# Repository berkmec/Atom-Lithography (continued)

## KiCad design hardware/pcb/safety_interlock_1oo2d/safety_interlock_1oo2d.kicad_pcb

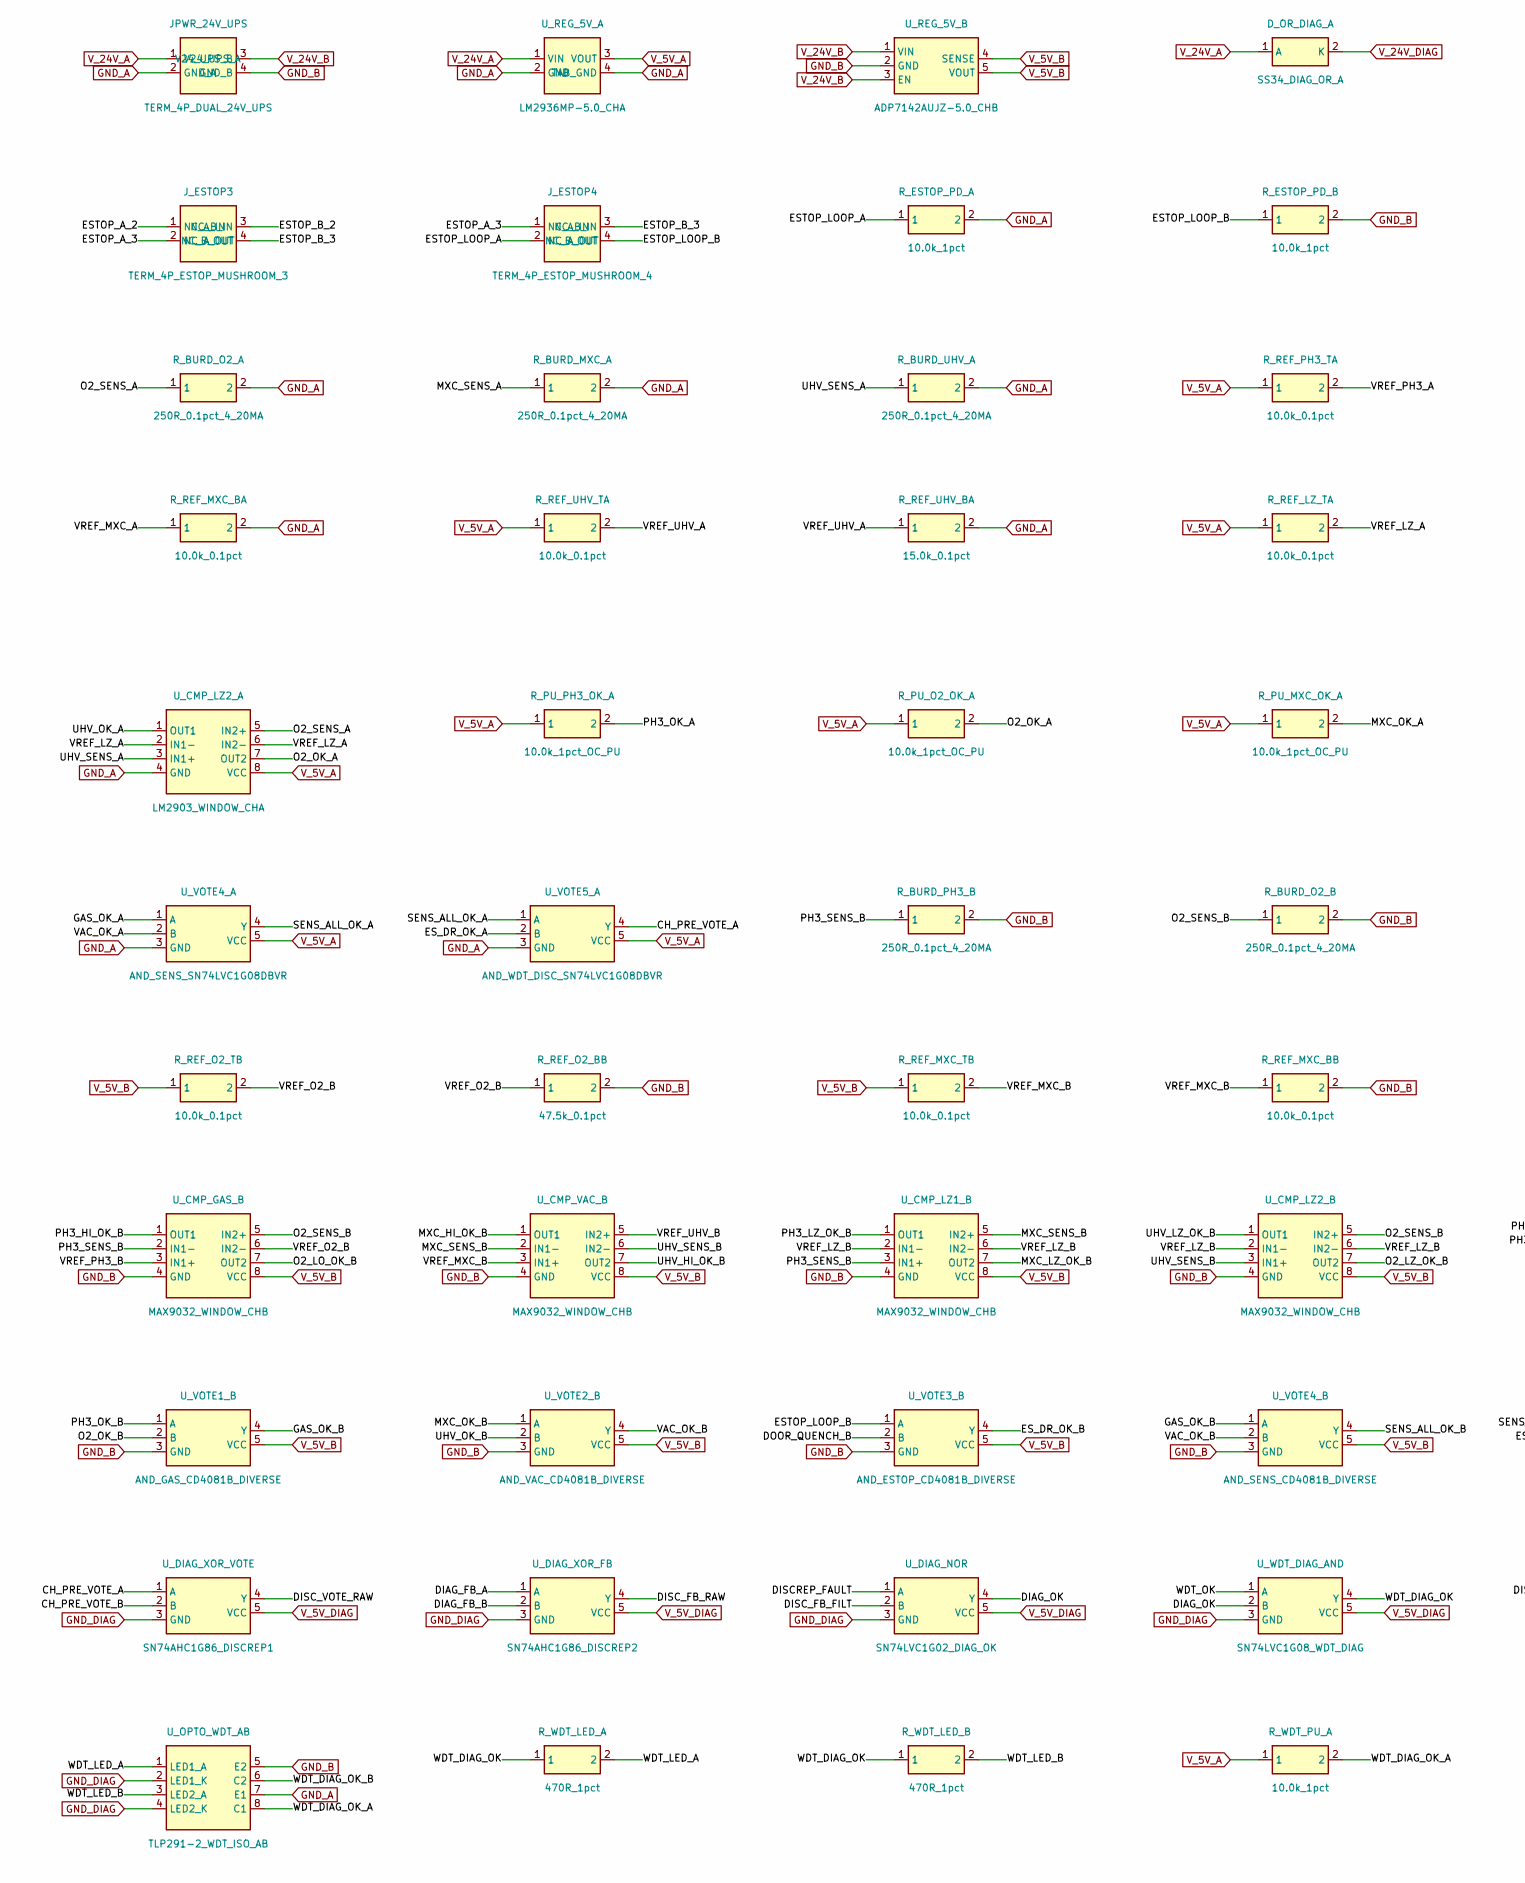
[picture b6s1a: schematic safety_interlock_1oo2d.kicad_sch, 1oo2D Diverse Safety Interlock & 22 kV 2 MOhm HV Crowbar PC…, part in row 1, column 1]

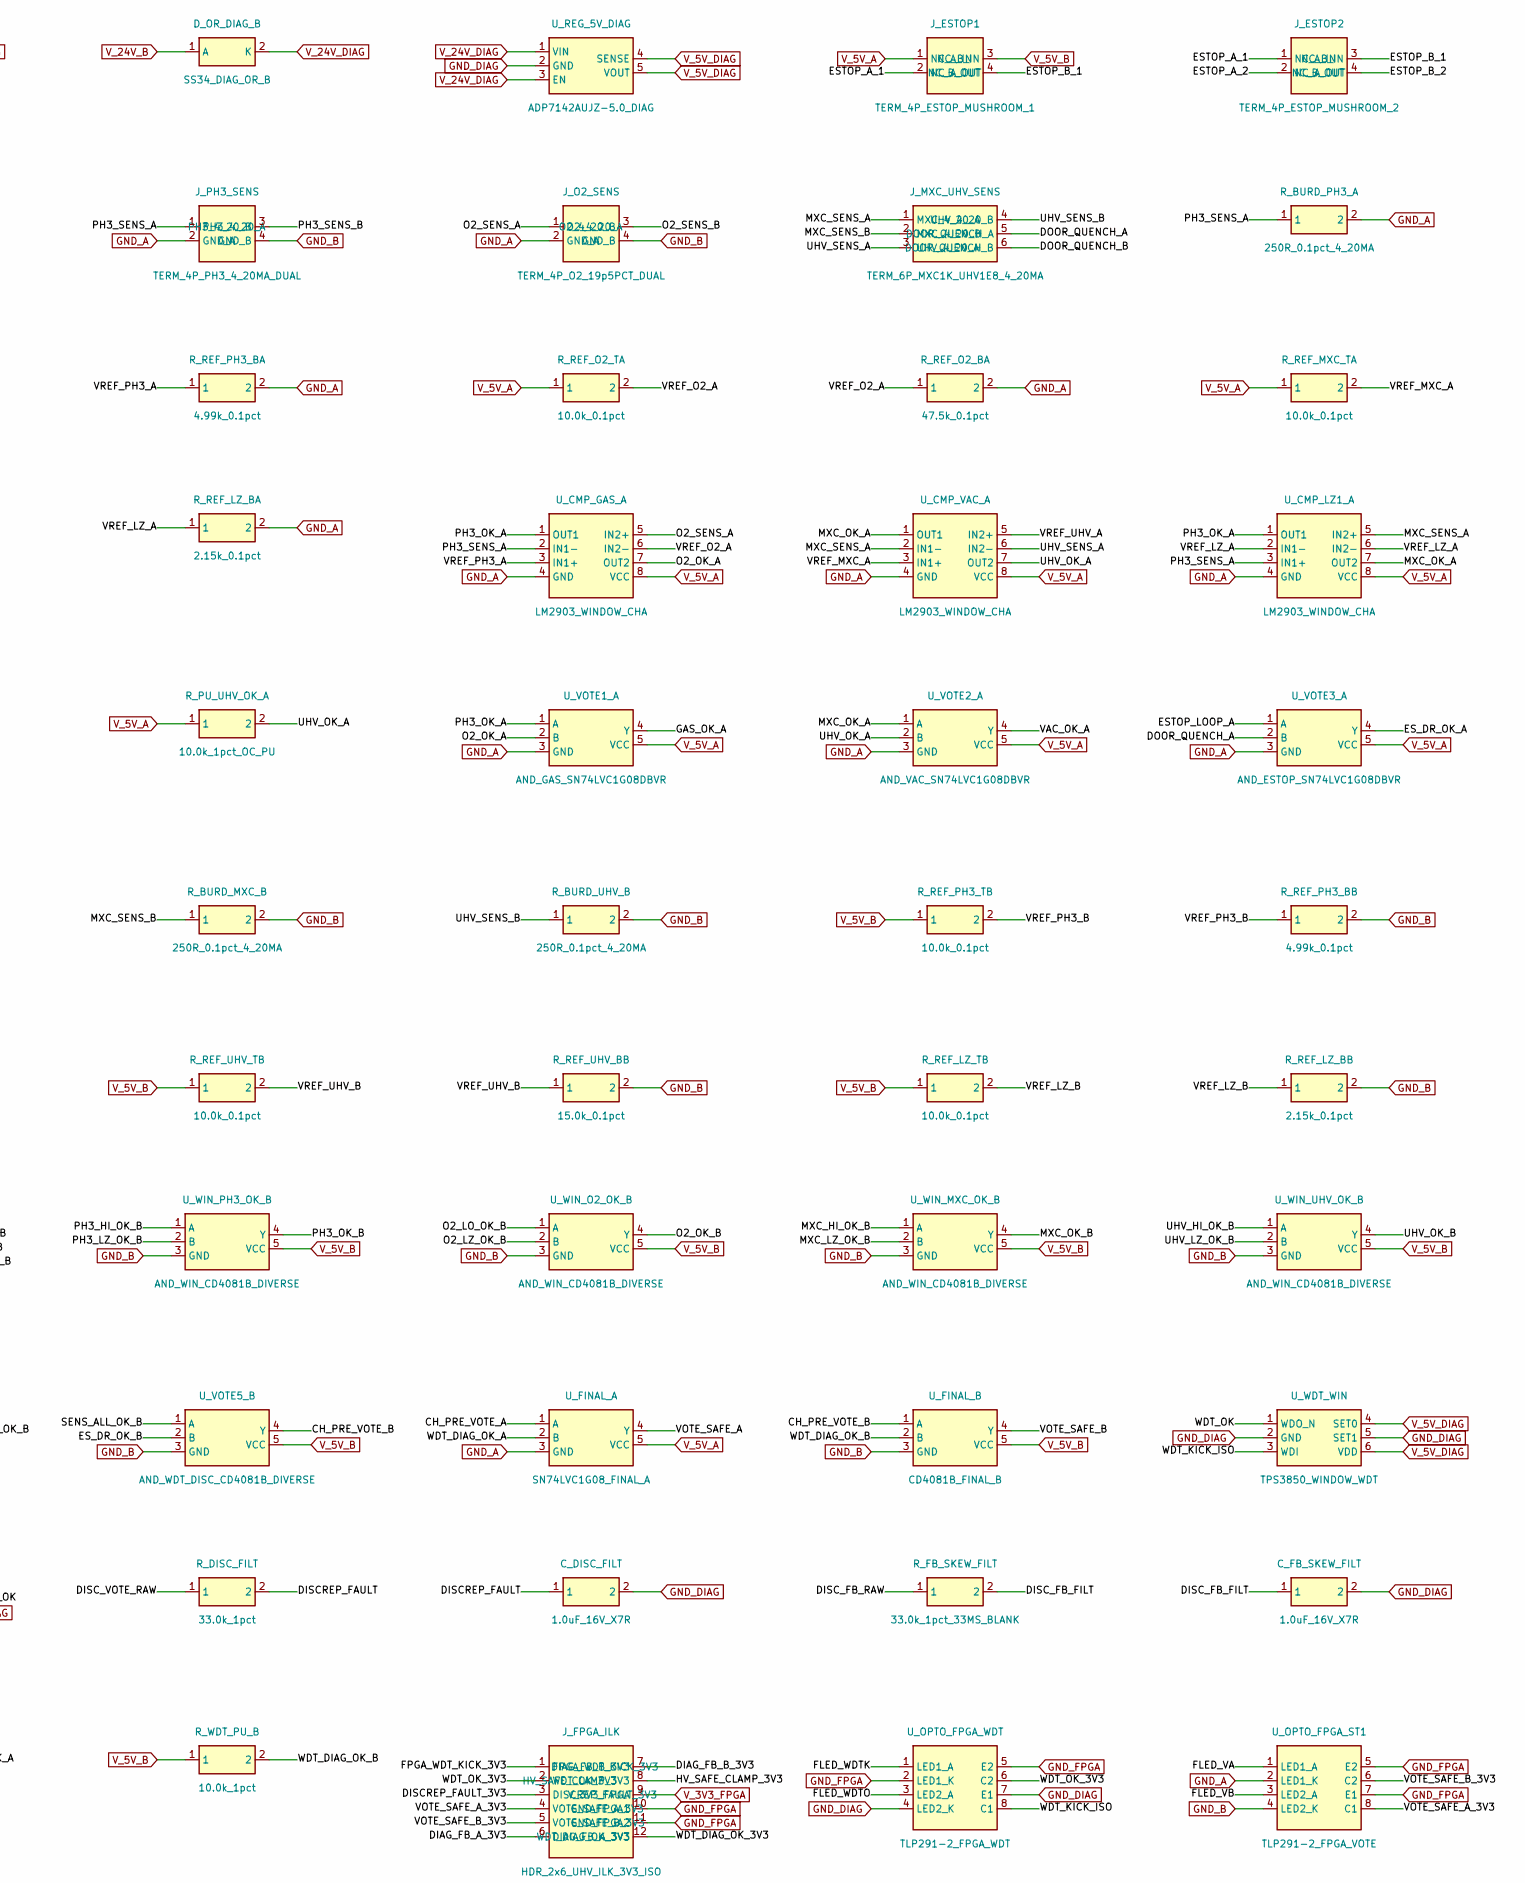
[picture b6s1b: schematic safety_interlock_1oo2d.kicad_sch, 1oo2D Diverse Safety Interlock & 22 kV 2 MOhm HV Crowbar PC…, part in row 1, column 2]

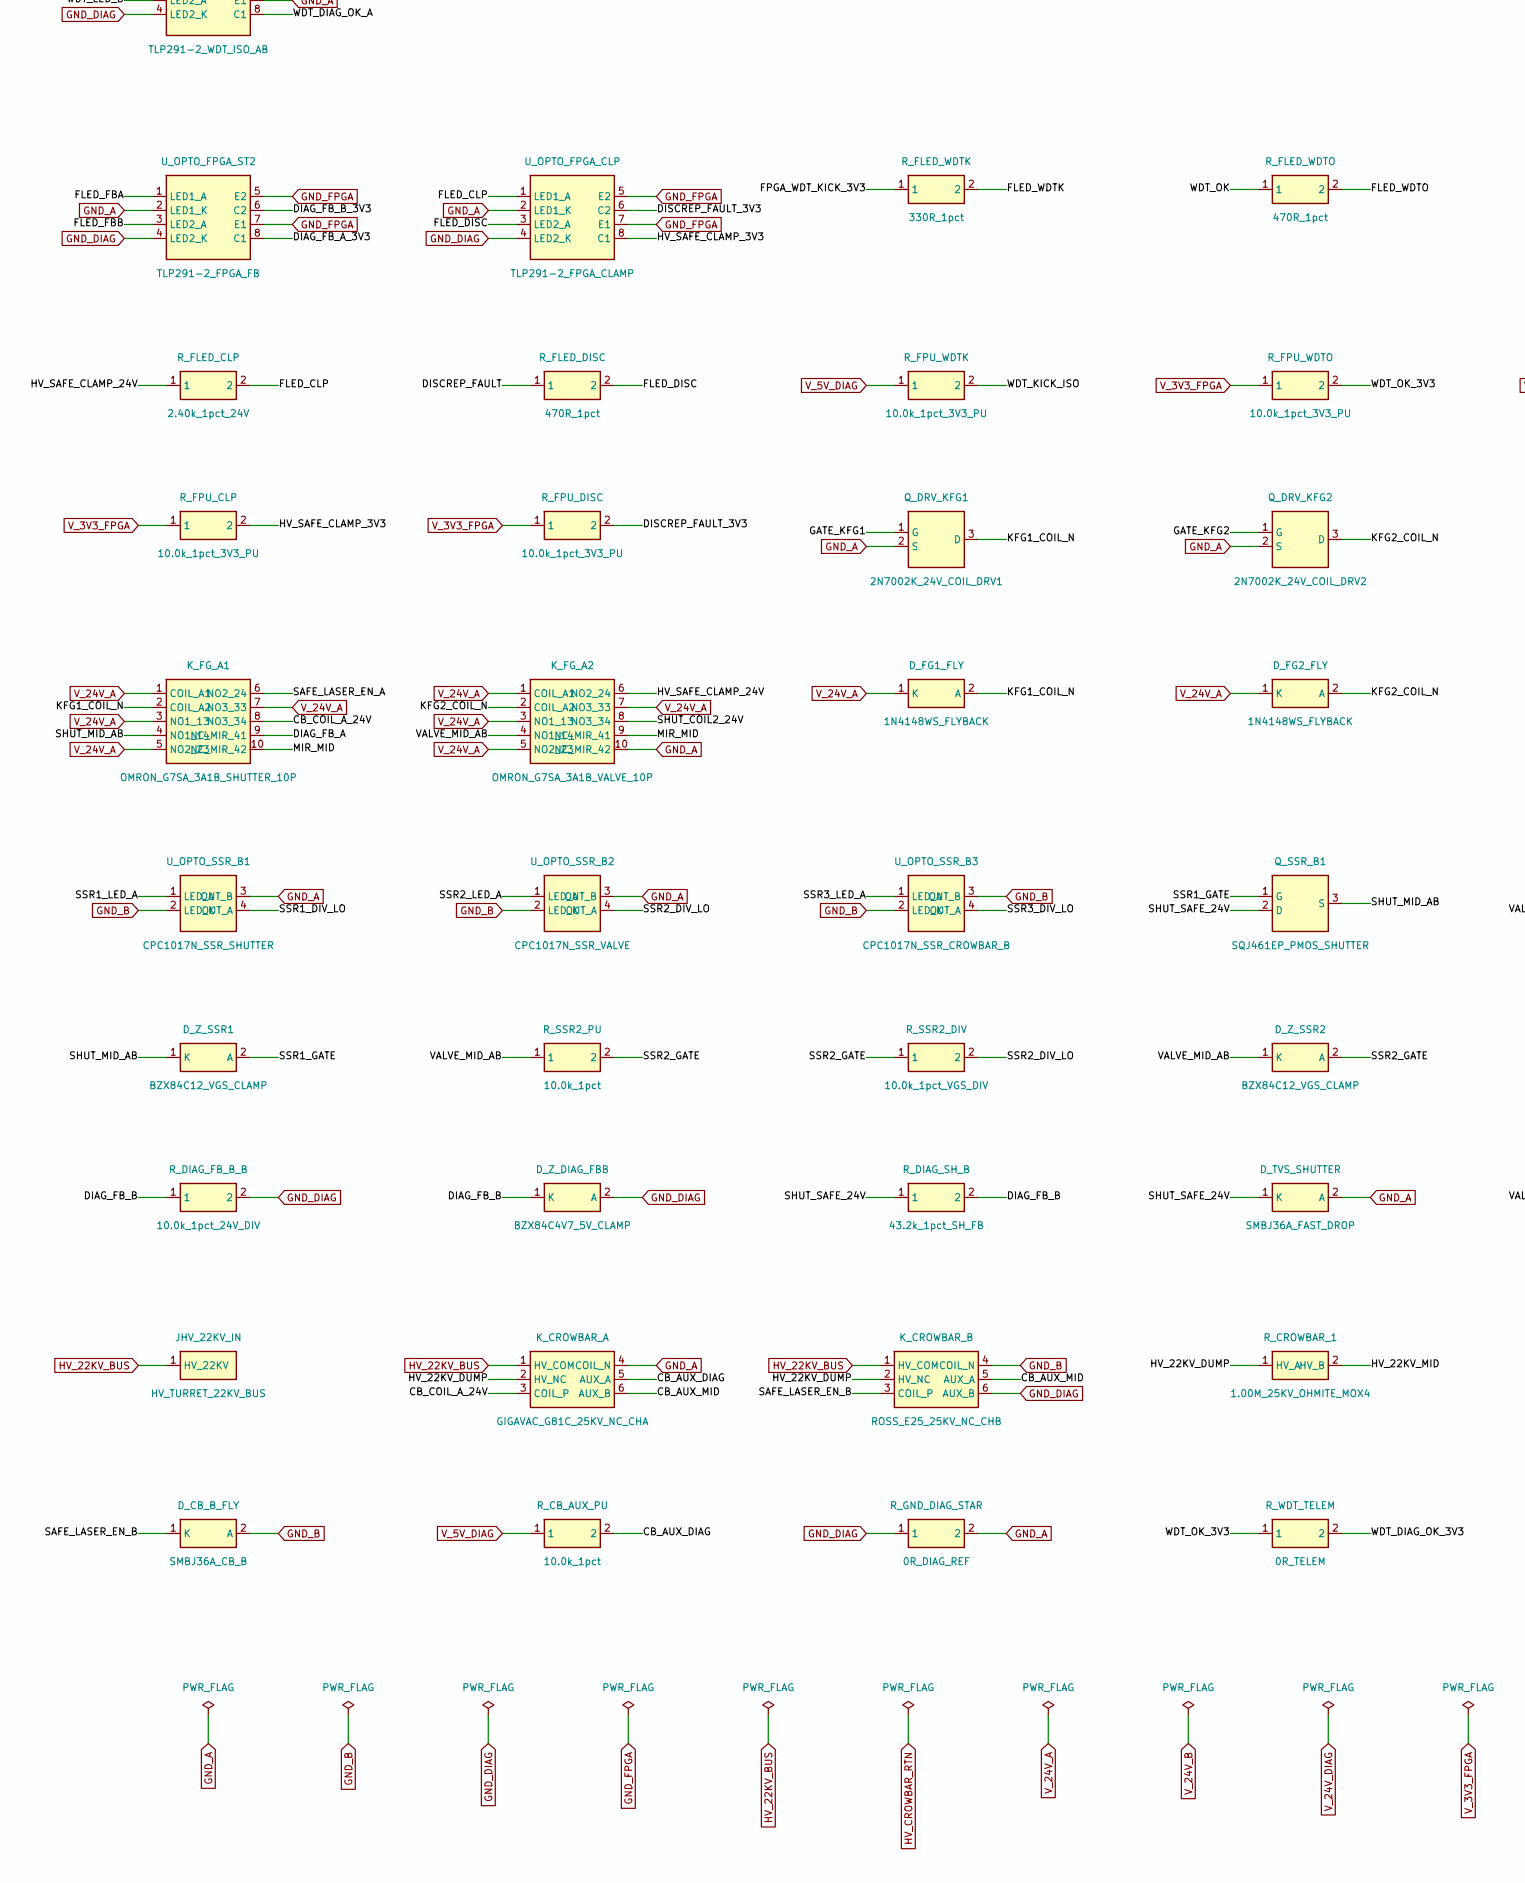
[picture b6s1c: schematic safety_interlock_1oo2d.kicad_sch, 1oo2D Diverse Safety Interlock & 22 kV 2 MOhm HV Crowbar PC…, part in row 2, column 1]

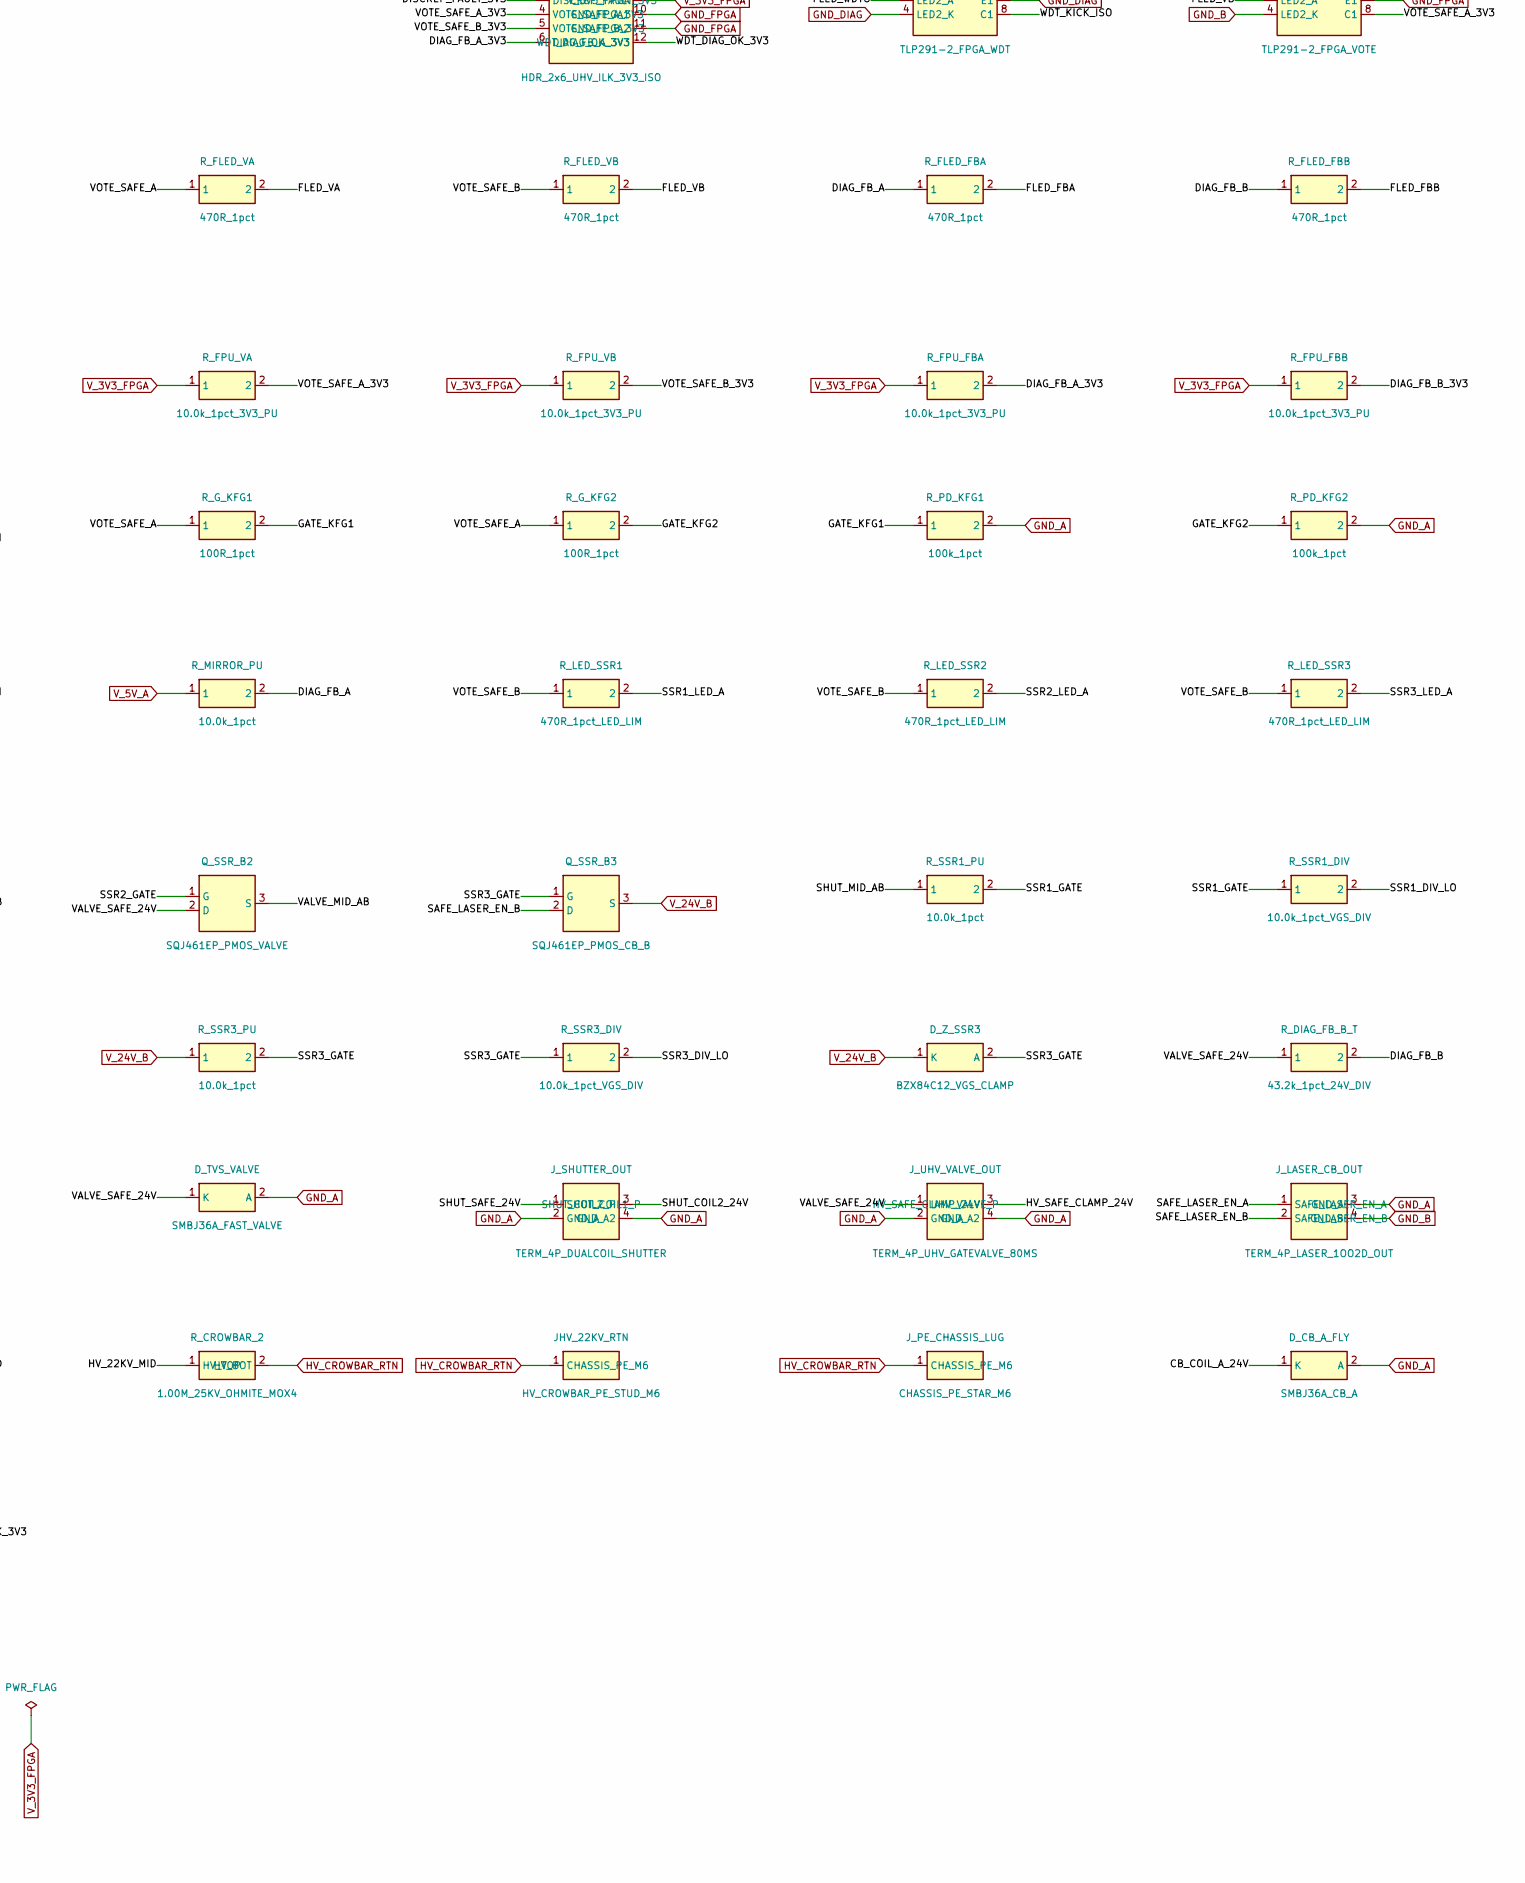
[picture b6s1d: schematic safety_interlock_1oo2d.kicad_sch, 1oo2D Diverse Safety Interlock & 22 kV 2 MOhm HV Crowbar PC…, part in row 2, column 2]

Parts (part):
C_DISC_FILT: 1.0uF_16V_X7R; C_0603_1608Metric; MPN 1.0uF_16V_X7R
C_FB_SKEW_FILT: 1.0uF_16V_X7R; C_0603_1608Metric; MPN 1.0uF_16V_X7R
D_CB_A_FLY: SMBJ36A_CB_A; D_1206_3216Metric; MPN SMBJ36A_CB_A
D_CB_B_FLY: SMBJ36A_CB_B; D_1206_3216Metric; MPN SMBJ36A_CB_B
D_FG1_FLY, D_FG2_FLY: 1N4148WS_FLYBACK; D_0805_2012Metric; MPN 1N4148WS_FLYBACK
D_OR_DIAG_A: SS34_DIAG_OR_A; D_0805_2012Metric; MPN SS34_DIAG_OR_A
D_OR_DIAG_B: SS34_DIAG_OR_B; D_0805_2012Metric; MPN SS34_DIAG_OR_B
D_TVS_SHUTTER: SMBJ36A_FAST_DROP; D_1206_3216Metric; MPN SMBJ36A_FAST_DROP
D_TVS_VALVE: SMBJ36A_FAST_VALVE; D_1206_3216Metric; MPN SMBJ36A_FAST_VALVE
D_Z_DIAG_FBB: BZX84C4V7_5V_CLAMP; D_0805_2012Metric; MPN BZX84C4V7_5V_CLAMP
D_Z_SSR1, D_Z_SSR2, D_Z_SSR3: BZX84C12_VGS_CLAMP; D_0805_2012Metric; MPN BZX84C12_VGS_CLAMP
JHV_22KV_IN: HV_TURRET_22KV_BUS; HV_ALUMINA_TURRET_25KV; MPN CeramTec_25kV_Alumina_Turret
JHV_22KV_RTN: HV_CROWBAR_PE_STUD_M6; PE_STAR_LUG_M6; MPN Keystone_PE_Star_Lug_M6
JPWR_24V_UPS: TERM_4P_DUAL_24V_UPS; HDR_1x4_5.08mm; MPN TERM_4P_DUAL_24V_UPS
J_ESTOP1: TERM_4P_ESTOP_MUSHROOM_1; HDR_1x4_2.54mm; MPN TERM_4P_ESTOP_MUSHROOM_1
J_ESTOP2: TERM_4P_ESTOP_MUSHROOM_2; HDR_1x4_2.54mm; MPN TERM_4P_ESTOP_MUSHROOM_2
J_ESTOP3: TERM_4P_ESTOP_MUSHROOM_3; HDR_1x4_2.54mm; MPN TERM_4P_ESTOP_MUSHROOM_3
J_ESTOP4: TERM_4P_ESTOP_MUSHROOM_4; HDR_1x4_2.54mm; MPN TERM_4P_ESTOP_MUSHROOM_4
J_FPGA_ILK: HDR_2x6_UHV_ILK_3V3_ISO; HDR_2x6_2.54mm; MPN HDR_2x6_UHV_ILK_3V3_ISO
J_LASER_CB_OUT: TERM_4P_LASER_1OO2D_OUT; HDR_1x4_2.54mm; MPN TERM_4P_LASER_1OO2D_OUT
J_MXC_UHV_SENS: TERM_6P_MXC1K_UHV1E8_4_20MA; HDR_1x6_2.54mm; MPN TERM_6P_MXC1K_UHV1E8_4_20MA
J_O2_SENS: TERM_4P_O2_19p5PCT_DUAL; HDR_1x4_2.54mm; MPN TERM_4P_O2_19p5PCT_DUAL
J_PE_CHASSIS_LUG: CHASSIS_PE_STAR_M6; PE_STAR_LUG_M6; MPN Keystone_PE_Star_Lug_M6
J_PH3_SENS: TERM_4P_PH3_4_20MA_DUAL; HDR_1x4_2.54mm; MPN TERM_4P_PH3_4_20MA_DUAL
J_SHUTTER_OUT: TERM_4P_DUALCOIL_SHUTTER; HDR_1x4_2.54mm; MPN TERM_4P_DUALCOIL_SHUTTER
J_UHV_VALVE_OUT: TERM_4P_UHV_GATEVALVE_80MS; HDR_1x4_2.54mm; MPN TERM_4P_UHV_GATEVALVE_80MS
K_CROWBAR_A: GIGAVAC_G81C_25KV_NC_CHA; HV25KV_VACUUM_RELAY_WIDE_P44_52mm; MPN Gigavac_G81C-25KV-NC
K_CROWBAR_B: ROSS_E25_25KV_NC_CHB; HV25KV_VACUUM_RELAY_WIDE_P44_52mm; MPN Ross_E25-NC-25KV
K_FG_A1: OMRON_G7SA_3A1B_SHUTTER_10P; OMRON_G7SA_3A1B_10P_THT; MPN Omron_G7SA-3A1B-DC24
K_FG_A2: OMRON_G7SA_3A1B_VALVE_10P; OMRON_G7SA_3A1B_10P_THT; MPN Omron_G7SA-3A1B-DC24
Q_DRV_KFG1: 2N7002K_24V_COIL_DRV1; SOT-23; MPN 2N7002K
Q_DRV_KFG2: 2N7002K_24V_COIL_DRV2; SOT-23; MPN 2N7002K
Q_SSR_B1: SQJ461EP_PMOS_SHUTTER; TO-252-2; MPN Vishay_SQJ461EP
Q_SSR_B2: SQJ461EP_PMOS_VALVE; TO-252-2; MPN Vishay_SQJ461EP
Q_SSR_B3: SQJ461EP_PMOS_CB_B; TO-252-2; MPN Vishay_SQJ461EP
R_BURD_MXC_A: 250R_0.1pct_4_20MA; R_0805_2012Metric; MPN 250R_0.1pct_4_20MA
R_BURD_MXC_B: 250R_0.1pct_4_20MA; R_0805_2012Metric; MPN 250R_0.1pct_4_20MA
R_BURD_O2_A, R_BURD_O2_B: 250R_0.1pct_4_20MA; R_0805_2012Metric; MPN 250R_0.1pct_4_20MA
R_BURD_PH3_A, R_BURD_PH3_B: 250R_0.1pct_4_20MA; R_0805_2012Metric; MPN 250R_0.1pct_4_20MA
R_BURD_UHV_A: 250R_0.1pct_4_20MA; R_0805_2012Metric; MPN 250R_0.1pct_4_20MA
R_BURD_UHV_B: 250R_0.1pct_4_20MA; R_0805_2012Metric; MPN 250R_0.1pct_4_20MA
R_CB_AUX_PU: 10.0k_1pct; R_0603_1608Metric; MPN 10.0k_1pct
R_CROWBAR_1: 1.00M_25KV_OHMITE_MOX4; OHMITE_MOX4_25KV_H20mm; MPN Ohmite_MOX400231004FE
R_CROWBAR_2: 1.00M_25KV_OHMITE_MOX4; OHMITE_MOX4_25KV_V52mm; MPN Ohmite_MOX400231004FE
R_DIAG_FB_B_B: 10.0k_1pct_24V_DIV; R_0805_2012Metric; MPN 10.0k_1pct_24V_DIV
R_DIAG_FB_B_T: 43.2k_1pct_24V_DIV; R_0805_2012Metric; MPN 43.2k_1pct_24V_DIV
R_DIAG_SH_B: 43.2k_1pct_SH_FB; R_0805_2012Metric; MPN 43.2k_1pct_SH_FB
R_DISC_FILT: 33.0k_1pct; R_0603_1608Metric; MPN 33.0k_1pct
R_ESTOP_PD_A: 10.0k_1pct; R_0805_2012Metric; MPN 10.0k_1pct
R_ESTOP_PD_B: 10.0k_1pct; R_0805_2012Metric; MPN 10.0k_1pct
R_FB_SKEW_FILT: 33.0k_1pct_33MS_BLANK; R_0603_1608Metric; MPN 33.0k_1pct_33MS_BLANK
R_FLED_CLP: 2.40k_1pct_24V; R_0603_1608Metric; MPN 2.40k_1pct_24V
R_FLED_DISC: 470R_1pct; R_0603_1608Metric; MPN 470R_1pct
R_FLED_FBA: 470R_1pct; R_0603_1608Metric; MPN 470R_1pct
R_FLED_FBB: 470R_1pct; R_0603_1608Metric; MPN 470R_1pct
R_FLED_VA: 470R_1pct; R_0603_1608Metric; MPN 470R_1pct
R_FLED_VB: 470R_1pct; R_0603_1608Metric; MPN 470R_1pct
R_FLED_WDTK: 330R_1pct; R_0603_1608Metric; MPN 330R_1pct
R_FLED_WDTO: 470R_1pct; R_0603_1608Metric; MPN 470R_1pct
R_FPU_CLP: 10.0k_1pct_3V3_PU; R_0603_1608Metric; MPN 10.0k_1pct_3V3_PU
R_FPU_DISC: 10.0k_1pct_3V3_PU; R_0603_1608Metric; MPN 10.0k_1pct_3V3_PU
R_FPU_FBA: 10.0k_1pct_3V3_PU; R_0603_1608Metric; MPN 10.0k_1pct_3V3_PU
R_FPU_FBB: 10.0k_1pct_3V3_PU; R_0603_1608Metric; MPN 10.0k_1pct_3V3_PU
R_FPU_VA: 10.0k_1pct_3V3_PU; R_0603_1608Metric; MPN 10.0k_1pct_3V3_PU
R_FPU_VB: 10.0k_1pct_3V3_PU; R_0603_1608Metric; MPN 10.0k_1pct_3V3_PU
R_FPU_WDTK: 10.0k_1pct_3V3_PU; R_0603_1608Metric; MPN 10.0k_1pct_3V3_PU
R_FPU_WDTO: 10.0k_1pct_3V3_PU; R_0603_1608Metric; MPN 10.0k_1pct_3V3_PU
R_GND_DIAG_STAR: 0R_DIAG_REF; R_0805_2012Metric; MPN 0R_DIAG_REF
R_G_KFG1, R_G_KFG2: 100R_1pct; R_0603_1608Metric; MPN 100R_1pct
R_LED_SSR1, R_LED_SSR2, R_LED_SSR3: 470R_1pct_LED_LIM; R_0603_1608Metric; MPN 470R_1pct_LED_LIM
R_MIRROR_PU: 10.0k_1pct; R_0603_1608Metric; MPN 10.0k_1pct
R_PD_KFG1, R_PD_KFG2: 100k_1pct; R_0603_1608Metric; MPN 100k_1pct
R_PU_MXC_OK_A: 10.0k_1pct_OC_PU; R_0603_1608Metric; MPN 10.0k_1pct_OC_PU
R_PU_O2_OK_A: 10.0k_1pct_OC_PU; R_0603_1608Metric; MPN 10.0k_1pct_OC_PU
R_PU_PH3_OK_A: 10.0k_1pct_OC_PU; R_0603_1608Metric; MPN 10.0k_1pct_OC_PU
R_PU_UHV_OK_A: 10.0k_1pct_OC_PU; R_0603_1608Metric; MPN 10.0k_1pct_OC_PU
R_REF_LZ_BA: 2.15k_0.1pct; R_0603_1608Metric; MPN 2.15k_0.1pct
R_REF_LZ_BB: 2.15k_0.1pct; R_0603_1608Metric; MPN 2.15k_0.1pct
R_REF_LZ_TA: 10.0k_0.1pct; R_0603_1608Metric; MPN 10.0k_0.1pct
R_REF_LZ_TB: 10.0k_0.1pct; R_0603_1608Metric; MPN 10.0k_0.1pct
R_REF_MXC_BA: 10.0k_0.1pct; R_0603_1608Metric; MPN 10.0k_0.1pct
R_REF_MXC_BB: 10.0k_0.1pct; R_0603_1608Metric; MPN 10.0k_0.1pct
R_REF_MXC_TA: 10.0k_0.1pct; R_0603_1608Metric; MPN 10.0k_0.1pct
R_REF_MXC_TB: 10.0k_0.1pct; R_0603_1608Metric; MPN 10.0k_0.1pct
R_REF_O2_BA, R_REF_O2_BB: 47.5k_0.1pct; R_0603_1608Metric; MPN 47.5k_0.1pct
R_REF_O2_TA, R_REF_O2_TB: 10.0k_0.1pct; R_0603_1608Metric; MPN 10.0k_0.1pct
R_REF_PH3_BA, R_REF_PH3_BB: 4.99k_0.1pct; R_0603_1608Metric; MPN 4.99k_0.1pct
R_REF_PH3_TA, R_REF_PH3_TB: 10.0k_0.1pct; R_0603_1608Metric; MPN 10.0k_0.1pct
R_REF_UHV_BA: 15.0k_0.1pct; R_0603_1608Metric; MPN 15.0k_0.1pct
R_REF_UHV_BB: 15.0k_0.1pct; R_0603_1608Metric; MPN 15.0k_0.1pct
R_REF_UHV_TA: 10.0k_0.1pct; R_0603_1608Metric; MPN 10.0k_0.1pct
R_REF_UHV_TB: 10.0k_0.1pct; R_0603_1608Metric; MPN 10.0k_0.1pct
R_SSR1_DIV, R_SSR2_DIV, R_SSR3_DIV: 10.0k_1pct_VGS_DIV; R_0805_2012Metric; MPN 10.0k_1pct_VGS_DIV
R_SSR1_PU, R_SSR2_PU, R_SSR3_PU: 10.0k_1pct; R_0805_2012Metric; MPN 10.0k_1pct
R_WDT_LED_A: 470R_1pct; R_0603_1608Metric; MPN 470R_1pct
R_WDT_LED_B: 470R_1pct; R_0603_1608Metric; MPN 470R_1pct
R_WDT_PU_A: 10.0k_1pct; R_0603_1608Metric; MPN 10.0k_1pct
R_WDT_PU_B: 10.0k_1pct; R_0603_1608Metric; MPN 10.0k_1pct
R_WDT_TELEM: 0R_TELEM; R_0603_1608Metric; MPN 0R_TELEM
U_CMP_GAS_A: LM2903_WINDOW_CHA; SOIC-8_3.9x4.9mm_P1.27mm; MPN LM2903DR
U_CMP_GAS_B: MAX9032_WINDOW_CHB; SOIC-8_3.9x4.9mm_P1.27mm; MPN MAX9032AKA
U_CMP_LZ1_A, U_CMP_LZ2_A: LM2903_WINDOW_CHA; SOIC-8_3.9x4.9mm_P1.27mm; MPN LM2903DR
U_CMP_LZ1_B, U_CMP_LZ2_B: MAX9032_WINDOW_CHB; SOIC-8_3.9x4.9mm_P1.27mm; MPN MAX9032AKA
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
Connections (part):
CB_AUX_DIAG: K_CROWBAR_A.5 (AUX_A), R_CB_AUX_PU.2
CB_AUX_MID: K_CROWBAR_A.6 (AUX_B), K_CROWBAR_B.5 (AUX_A)
CB_COIL_A_24V: D_CB_A_FLY.1 (K), K_CROWBAR_A.3 (COIL_P), K_FG_A1.8 (NO3_34)
CH_PRE_VOTE_A: U_DIAG_XOR_VOTE.1 (A), U_FINAL_A.1 (A), U_VOTE5_A.4 (Y)
CH_PRE_VOTE_B: U_DIAG_XOR_VOTE.2 (B), U_FINAL_B.1 (A), U_VOTE5_B.4 (Y)
DIAG_FB_A: K_FG_A1.9 (NC_MIR_41), R_FLED_FBA.1, R_MIRROR_PU.2, U_DIAG_XOR_FB.1 (A)
DIAG_FB_A_3V3: J_FPGA_ILK.6 (DIAG_FB_A_3V3), R_FPU_FBA.2, U_OPTO_FPGA_ST2.8 (C1)
DIAG_FB_B: D_Z_DIAG_FBB.1 (K), R_DIAG_FB_B_B.1, R_DIAG_FB_B_T.2, R_DIAG_SH_B.2, R_FLED_FBB.1, U_DIAG_XOR_FB.2 (B)
DIAG_FB_B_3V3: J_FPGA_ILK.7 (DIAG_FB_B_3V3), R_FPU_FBB.2, U_OPTO_FPGA_ST2.6 (C2)
DIAG_OK: U_DIAG_NOR.4 (Y), U_WDT_DIAG_AND.2 (B)
DISCREP_FAULT: C_DISC_FILT.1, R_DISC_FILT.2, R_FLED_DISC.1, U_DIAG_NOR.1 (A)
DISCREP_FAULT_3V3: J_FPGA_ILK.3 (DISCREP_FAULT_3V3), R_FPU_DISC.2, U_OPTO_FPGA_CLP.6 (C2)
DISC_FB_FILT: C_FB_SKEW_FILT.1, R_FB_SKEW_FILT.2, U_DIAG_NOR.2 (B)
DISC_FB_RAW: R_FB_SKEW_FILT.1, U_DIAG_XOR_FB.4 (Y)
DISC_VOTE_RAW: R_DISC_FILT.1, U_DIAG_XOR_VOTE.4 (Y)
DOOR_QUENCH_A: J_MXC_UHV_SENS.5 (DOOR_QUENCH_A), U_VOTE3_A.2 (B)
DOOR_QUENCH_B: J_MXC_UHV_SENS.6 (DOOR_QUENCH_B), U_VOTE3_B.2 (B)
ESTOP_A_1: J_ESTOP1.2 (NC_A_OUT), J_ESTOP2.1 (NC_A_IN)
ESTOP_A_2: J_ESTOP2.2 (NC_A_OUT), J_ESTOP3.1 (NC_A_IN)
ESTOP_A_3: J_ESTOP3.2 (NC_A_OUT), J_ESTOP4.1 (NC_A_IN)
ESTOP_B_1: J_ESTOP1.4 (NC_B_OUT), J_ESTOP2.3 (NC_B_IN)
ESTOP_B_2: J_ESTOP2.4 (NC_B_OUT), J_ESTOP3.3 (NC_B_IN)
ESTOP_B_3: J_ESTOP3.4 (NC_B_OUT), J_ESTOP4.3 (NC_B_IN)
ESTOP_LOOP_A: J_ESTOP4.2 (NC_A_OUT), R_ESTOP_PD_A.1, U_VOTE3_A.1 (A)
ESTOP_LOOP_B: J_ESTOP4.4 (NC_B_OUT), R_ESTOP_PD_B.1, U_VOTE3_B.1 (A)
ES_DR_OK_A: U_VOTE3_A.4 (Y), U_VOTE5_A.2 (B)
ES_DR_OK_B: U_VOTE3_B.4 (Y), U_VOTE5_B.2 (B)
FLED_CLP: R_FLED_CLP.2, U_OPTO_FPGA_CLP.1 (LED1_A)
FLED_DISC: R_FLED_DISC.2, U_OPTO_FPGA_CLP.3 (LED2_A)
FLED_FBA: R_FLED_FBA.2, U_OPTO_FPGA_ST2.1 (LED1_A)
FLED_FBB: R_FLED_FBB.2, U_OPTO_FPGA_ST2.3 (LED2_A)
FLED_VA: R_FLED_VA.2, U_OPTO_FPGA_ST1.1 (LED1_A)
FLED_VB: R_FLED_VB.2, U_OPTO_FPGA_ST1.3 (LED2_A)
FLED_WDTK: R_FLED_WDTK.2, U_OPTO_FPGA_WDT.1 (LED1_A)
FLED_WDTO: R_FLED_WDTO.2, U_OPTO_FPGA_WDT.3 (LED2_A)
FPGA_WDT_KICK_3V3: J_FPGA_ILK.1 (FPGA_WDT_KICK_3V3), R_FLED_WDTK.1
GAS_OK_A: U_VOTE1_A.4 (Y), U_VOTE4_A.1 (A)
GAS_OK_B: U_VOTE1_B.4 (Y), U_VOTE4_B.1 (A)
GATE_KFG1: Q_DRV_KFG1.1 (G), R_G_KFG1.2, R_PD_KFG1.1
GATE_KFG2: Q_DRV_KFG2.1 (G), R_G_KFG2.2, R_PD_KFG2.1
GND_A: D_CB_A_FLY.2 (A), D_TVS_SHUTTER.2 (A), D_TVS_VALVE.2 (A), JPWR_24V_UPS.2 (GND_A), J_LASER_CB_OUT.3 (GND_A), J_O2_SENS.2 (GND_A), J_PH3_SENS.2 (GND_A), J_SHUTTER_OUT.2 (GND_A), J_SHUTTER_OUT.4 (GND_A2), J_UHV_VALVE_OUT.2 (GND_A), J_UHV_VALVE_OUT.4 (GND_A2), K_CROWBAR_A.4 (COIL_N), K_FG_A2.10 (NC_MIR_42), Q_DRV_KFG1.2 (S), Q_DRV_KFG2.2 (S), R_BURD_MXC_A.2, R_BURD_O2_A.2, R_BURD_PH3_A.2, R_BURD_UHV_A.2, R_ESTOP_PD_A.2, R_GND_DIAG_STAR.2, R_PD_KFG1.2, R_PD_KFG2.2, R_REF_LZ_BA.2, R_REF_MXC_BA.2, R_REF_O2_BA.2, R_REF_PH3_BA.2, R_REF_UHV_BA.2, U_CMP_GAS_A.4 (GND), U_CMP_LZ1_A.4 (GND), U_CMP_LZ2_A.4 (GND), U_CMP_VAC_A.4 (GND), U_FINAL_A.3 (GND), U_OPTO_FPGA_CLP.2 (LED1_K), U_OPTO_FPGA_ST1.2 (LED1_K), U_OPTO_FPGA_ST2.2 (LED1_K), U_OPTO_SSR_B1.3 (OUT_B), U_OPTO_SSR_B2.3 (OUT_B), U_OPTO_WDT_AB.7 (E1), U_REG_5V_A.2 (GND), U_REG_5V_A.4 (TAB_GND), U_VOTE1_A.3 (GND), U_VOTE2_A.3 (GND), U_VOTE3_A.3 (GND), U_VOTE4_A.3 (GND), U_VOTE5_A.3 (GND)
GND_B: D_CB_B_FLY.2 (A), JPWR_24V_UPS.4 (GND_B), J_LASER_CB_OUT.4 (GND_B), J_O2_SENS.4 (GND_B), J_PH3_SENS.4 (GND_B), K_CROWBAR_B.4 (COIL_N), R_BURD_MXC_B.2, R_BURD_O2_B.2, R_BURD_PH3_B.2, R_BURD_UHV_B.2, R_ESTOP_PD_B.2, R_REF_LZ_BB.2, R_REF_MXC_BB.2, R_REF_O2_BB.2, R_REF_PH3_BB.2, R_REF_UHV_BB.2, U_CMP_GAS_B.4 (GND), U_CMP_LZ1_B.4 (GND), U_CMP_LZ2_B.4 (GND), U_CMP_VAC_B.4 (GND), U_FINAL_B.3 (GND), U_OPTO_FPGA_ST1.4 (LED2_K), U_OPTO_SSR_B1.2 (LED_K), U_OPTO_SSR_B2.2 (LED_K), U_OPTO_SSR_B3.2 (LED_K), U_OPTO_SSR_B3.3 (OUT_B), U_OPTO_WDT_AB.5 (E2), U_REG_5V_B.2 (GND), U_VOTE1_B.3 (GND), U_VOTE2_B.3 (GND), U_VOTE3_B.3 (GND), U_VOTE4_B.3 (GND), U_VOTE5_B.3 (GND), U_WIN_MXC_OK_B.3 (GND), U_WIN_O2_OK_B.3 (GND), U_WIN_PH3_OK_B.3 (GND), U_WIN_UHV_OK_B.3 (GND)
GND_DIAG: C_DISC_FILT.2, C_FB_SKEW_FILT.2, D_Z_DIAG_FBB.2 (A), K_CROWBAR_B.6 (AUX_B), R_DIAG_FB_B_B.2, R_GND_DIAG_STAR.1, U_DIAG_NOR.3 (GND), U_DIAG_XOR_FB.3 (GND), U_DIAG_XOR_VOTE.3 (GND), U_OPTO_FPGA_CLP.4 (LED2_K), U_OPTO_FPGA_ST2.4 (LED2_K), U_OPTO_FPGA_WDT.4 (LED2_K), U_OPTO_FPGA_WDT.7 (E1), U_OPTO_WDT_AB.2 (LED1_K), U_OPTO_WDT_AB.4 (LED2_K), U_REG_5V_DIAG.2 (GND), U_WDT_DIAG_AND.3 (GND), U_WDT_WIN.2 (GND), U_WDT_WIN.5 (SET1)
GND_FPGA: J_FPGA_ILK.10 (GND_FPGA1), J_FPGA_ILK.11 (GND_FPGA2), U_OPTO_FPGA_CLP.5 (E2), U_OPTO_FPGA_CLP.7 (E1), U_OPTO_FPGA_ST1.5 (E2), U_OPTO_FPGA_ST1.7 (E1), U_OPTO_FPGA_ST2.5 (E2), U_OPTO_FPGA_ST2.7 (E1), U_OPTO_FPGA_WDT.2 (LED1_K), U_OPTO_FPGA_WDT.5 (E2)
HV_22KV_BUS: JHV_22KV_IN.1, K_CROWBAR_A.1 (HV_COM), K_CROWBAR_B.1 (HV_COM)
HV_22KV_DUMP: K_CROWBAR_A.2 (HV_NC), K_CROWBAR_B.2 (HV_NC), R_CROWBAR_1.1 (HV_A)
HV_22KV_MID: R_CROWBAR_1.2 (HV_B), R_CROWBAR_2.1 (HV_TOP)
HV_CROWBAR_RTN: JHV_22KV_RTN.1, J_PE_CHASSIS_LUG.1, R_CROWBAR_2.2 (HV_BOT)
HV_SAFE_CLAMP_3V3: J_FPGA_ILK.8 (HV_SAFE_CLAMP_3V3), R_FPU_CLP.2, U_OPTO_FPGA_CLP.8 (C1)
HV_SAFE_CLAMP_24V: J_UHV_VALVE_OUT.3 (HV_SAFE_CLAMP_24V), K_FG_A2.6 (NO2_24), R_FLED_CLP.1
KFG1_COIL_N: D_FG1_FLY.2 (A), K_FG_A1.2 (COIL_A2), Q_DRV_KFG1.3 (D)
KFG2_COIL_N: D_FG2_FLY.2 (A), K_FG_A2.2 (COIL_A2), Q_DRV_KFG2.3 (D)
MIR_MID: K_FG_A1.10 (NC_MIR_42), K_FG_A2.9 (NC_MIR_41)
MXC_HI_OK_B: U_CMP_VAC_B.1 (OUT1), U_WIN_MXC_OK_B.1 (A)
MXC_LZ_OK_B: U_CMP_LZ1_B.7 (OUT2), U_WIN_MXC_OK_B.2 (B)
MXC_OK_A: R_PU_MXC_OK_A.2, U_CMP_LZ1_A.7 (OUT2), U_CMP_VAC_A.1 (OUT1), U_VOTE2_A.1 (A)
MXC_OK_B: U_VOTE2_B.1 (A), U_WIN_MXC_OK_B.4 (Y)
MXC_SENS_A: J_MXC_UHV_SENS.1 (MXC_4_20_A), R_BURD_MXC_A.1, U_CMP_LZ1_A.5 (IN2+), U_CMP_VAC_A.2 (IN1-)
MXC_SENS_B: J_MXC_UHV_SENS.2 (MXC_4_20_B), R_BURD_MXC_B.1, U_CMP_LZ1_B.5 (IN2+), U_CMP_VAC_B.2 (IN1-)
O2_LO_OK_B: U_CMP_GAS_B.7 (OUT2), U_WIN_O2_OK_B.1 (A)
O2_LZ_OK_B: U_CMP_LZ2_B.7 (OUT2), U_WIN_O2_OK_B.2 (B)
O2_OK_A: R_PU_O2_OK_A.2, U_CMP_GAS_A.7 (OUT2), U_CMP_LZ2_A.7 (OUT2), U_VOTE1_A.2 (B)
O2_OK_B: U_VOTE1_B.2 (B), U_WIN_O2_OK_B.4 (Y)
O2_SENS_A: J_O2_SENS.1 (O2_4_20_A), R_BURD_O2_A.1, U_CMP_GAS_A.5 (IN2+), U_CMP_LZ2_A.5 (IN2+)
O2_SENS_B: J_O2_SENS.3 (O2_4_20_B), R_BURD_O2_B.1, U_CMP_GAS_B.5 (IN2+), U_CMP_LZ2_B.5 (IN2+)
PH3_HI_OK_B: U_CMP_GAS_B.1 (OUT1), U_WIN_PH3_OK_B.1 (A)
PH3_LZ_OK_B: U_CMP_LZ1_B.1 (OUT1), U_WIN_PH3_OK_B.2 (B)
PH3_OK_A: R_PU_PH3_OK_A.2, U_CMP_GAS_A.1 (OUT1), U_CMP_LZ1_A.1 (OUT1), U_VOTE1_A.1 (A)
PH3_OK_B: U_VOTE1_B.1 (A), U_WIN_PH3_OK_B.4 (Y)
PH3_SENS_A: J_PH3_SENS.1 (PH3_4_20_A), R_BURD_PH3_A.1, U_CMP_GAS_A.2 (IN1-), U_CMP_LZ1_A.3 (IN1+)
PH3_SENS_B: J_PH3_SENS.3 (PH3_4_20_B), R_BURD_PH3_B.1, U_CMP_GAS_B.2 (IN1-), U_CMP_LZ1_B.3 (IN1+)
SAFE_LASER_EN_A: J_LASER_CB_OUT.1 (SAFE_LASER_EN_A), K_FG_A1.6 (NO2_24)
SAFE_LASER_EN_B: D_CB_B_FLY.1 (K), J_LASER_CB_OUT.2 (SAFE_LASER_EN_B), K_CROWBAR_B.3 (COIL_P), Q_SSR_B3.2 (D)
SENS_ALL_OK_A: U_VOTE4_A.4 (Y), U_VOTE5_A.1 (A)
SENS_ALL_OK_B: U_VOTE4_B.4 (Y), U_VOTE5_B.1 (A)
SHUT_COIL2_24V: J_SHUTTER_OUT.3 (SHUT_COIL2_P), K_FG_A2.8 (NO3_34)
SHUT_MID_AB: D_Z_SSR1.1 (K), K_FG_A1.4 (NO1_14), Q_SSR_B1.3 (S), R_SSR1_PU.1
SHUT_SAFE_24V: D_TVS_SHUTTER.1 (K), J_SHUTTER_OUT.1 (SHUT_COIL1_P), Q_SSR_B1.2 (D), R_DIAG_SH_B.1
SSR1_DIV_LO: R_SSR1_DIV.2, U_OPTO_SSR_B1.4 (OUT_A)
SSR1_GATE: D_Z_SSR1.2 (A), Q_SSR_B1.1 (G), R_SSR1_DIV.1, R_SSR1_PU.2
SSR1_LED_A: R_LED_SSR1.2, U_OPTO_SSR_B1.1 (LED_A)
SSR2_DIV_LO: R_SSR2_DIV.2, U_OPTO_SSR_B2.4 (OUT_A)
SSR2_GATE: D_Z_SSR2.2 (A), Q_SSR_B2.1 (G), R_SSR2_DIV.1, R_SSR2_PU.2
SSR2_LED_A: R_LED_SSR2.2, U_OPTO_SSR_B2.1 (LED_A)
SSR3_DIV_LO: R_SSR3_DIV.2, U_OPTO_SSR_B3.4 (OUT_A)
SSR3_GATE: D_Z_SSR3.2 (A), Q_SSR_B3.1 (G), R_SSR3_DIV.1, R_SSR3_PU.2
SSR3_LED_A: R_LED_SSR3.2, U_OPTO_SSR_B3.1 (LED_A)
UHV_HI_OK_B: U_CMP_VAC_B.7 (OUT2), U_WIN_UHV_OK_B.1 (A)
UHV_LZ_OK_B: U_CMP_LZ2_B.1 (OUT1), U_WIN_UHV_OK_B.2 (B)
UHV_OK_A: R_PU_UHV_OK_A.2, U_CMP_LZ2_A.1 (OUT1), U_CMP_VAC_A.7 (OUT2), U_VOTE2_A.2 (B)
UHV_OK_B: U_VOTE2_B.2 (B), U_WIN_UHV_OK_B.4 (Y)
UHV_SENS_A: J_MXC_UHV_SENS.3 (UHV_4_20_A), R_BURD_UHV_A.1, U_CMP_LZ2_A.3 (IN1+), U_CMP_VAC_A.6 (IN2-)
UHV_SENS_B: J_MXC_UHV_SENS.4 (UHV_4_20_B), R_BURD_UHV_B.1, U_CMP_LZ2_B.3 (IN1+), U_CMP_VAC_B.6 (IN2-)
VAC_OK_A: U_VOTE2_A.4 (Y), U_VOTE4_A.2 (B)
VAC_OK_B: U_VOTE2_B.4 (Y), U_VOTE4_B.2 (B)
VALVE_MID_AB: D_Z_SSR2.1 (K), K_FG_A2.4 (NO1_14), Q_SSR_B2.3 (S), R_SSR2_PU.1
VALVE_SAFE_24V: D_TVS_VALVE.1 (K), J_UHV_VALVE_OUT.1 (UHV_VALVE_P), Q_SSR_B2.2 (D), R_DIAG_FB_B_T.1
VOTE_SAFE_A: R_FLED_VA.1, R_G_KFG1.1, R_G_KFG2.1, U_FINAL_A.4 (Y)
VOTE_SAFE_A_3V3: J_FPGA_ILK.4 (VOTE_SAFE_A_3V3), R_FPU_VA.2, U_OPTO_FPGA_ST1.8 (C1)
VOTE_SAFE_B: R_FLED_VB.1, R_LED_SSR1.1, R_LED_SSR2.1, R_LED_SSR3.1, U_FINAL_B.4 (Y)
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
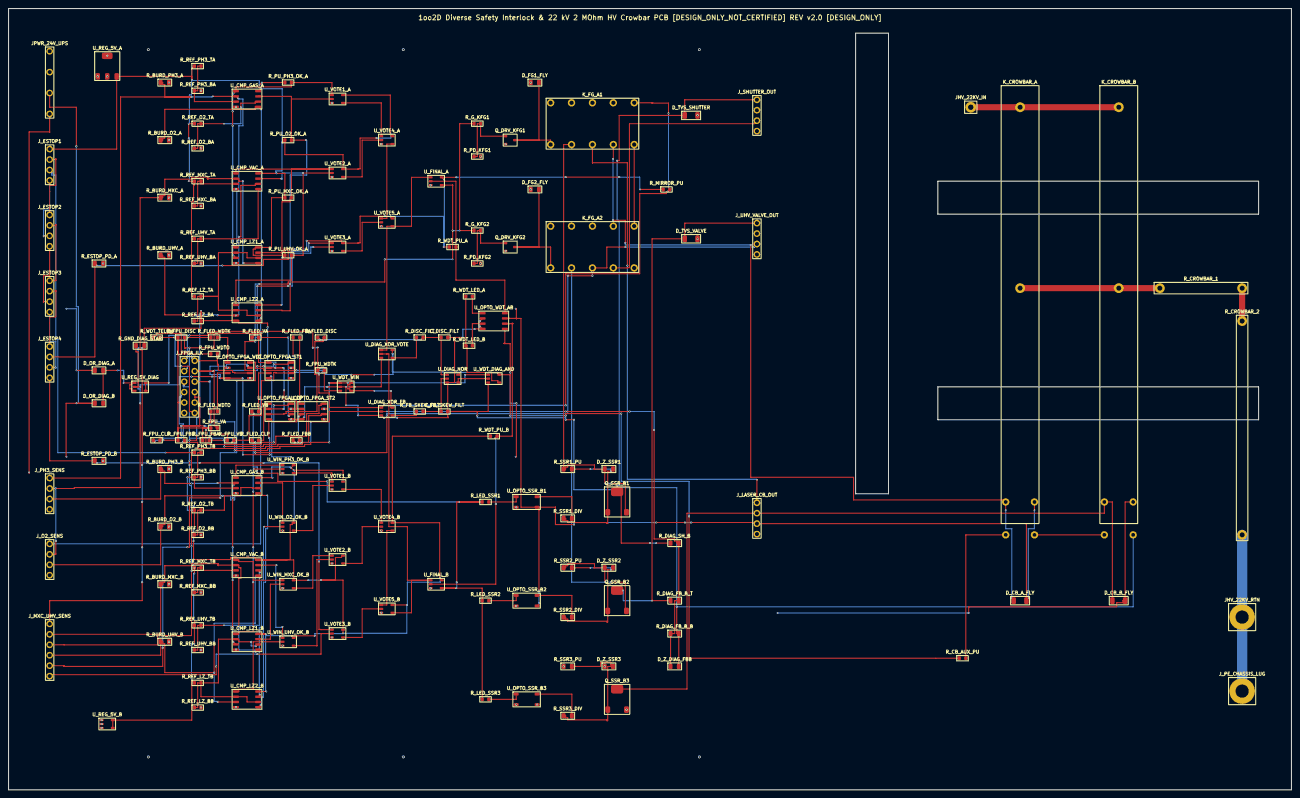
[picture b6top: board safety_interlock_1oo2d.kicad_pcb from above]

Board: 4 copper layers, 312.0 x 190.0 mm, 156 parts (0 on the bottom side), 127 nets.
